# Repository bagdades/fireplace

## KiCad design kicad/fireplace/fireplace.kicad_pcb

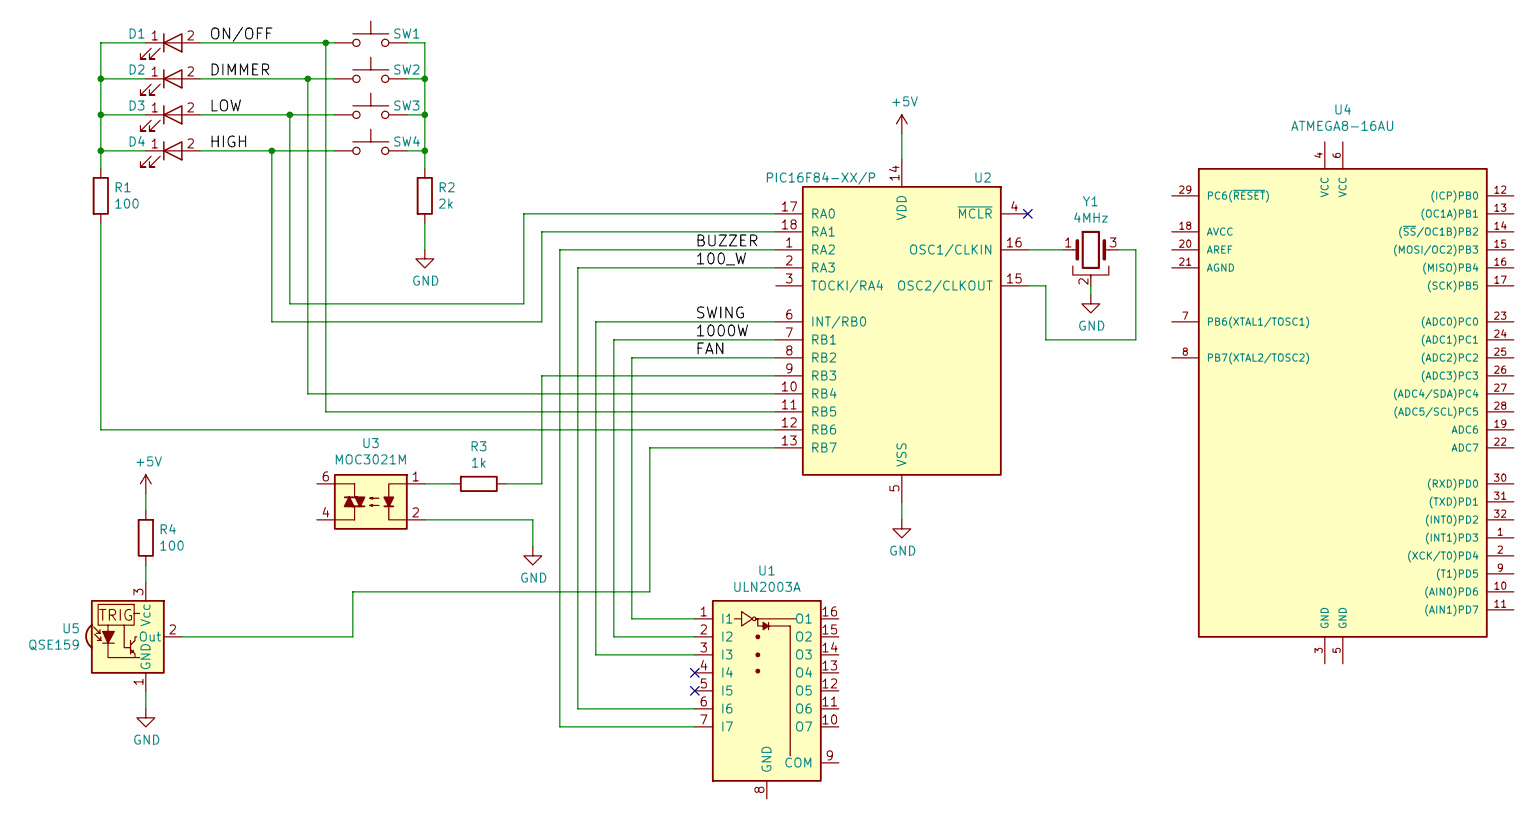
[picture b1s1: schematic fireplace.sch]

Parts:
D1, D2, D3, D4: LED; LED_D4.0mm
R1, R4: 100; R_Axial_DIN0309_L9.0mm_D3.2mm_P12.70mm_Horizontal
R2: 2k; R_Axial_DIN0309_L9.0mm_D3.2mm_P12.70mm_Horizontal
R3: 1k; R_Axial_DIN0309_L9.0mm_D3.2mm_P12.70mm_Horizontal
SW1, SW2, SW3, SW4: SW_Push; SW_PUSH_6mm_h5mm
U1: ULN2003A; DIP-16_W7.62mm
U2: PIC16F84-XX/P; DIP-18_W7.62mm
U3: MOC3021M; DIP-6_W7.62mm
U4: ATMEGA8-16AU; LQFP-32_7x7mm_Pitch0.8mm
U5: QSE159; ONSemi_QSE15x
Y1: 4MHz; Resonator-3pin_w8.0mm_h3.5mm

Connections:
+5V: R4.2, U2.14 (VDD)
/100_W: U1.6 (I6), U2.2 (RA3)
/1000W: U1.2 (I2), U2.7 (RB1)
/BUZZER: U1.7 (I7), U2.1 (RA2)
/DIMMER: D2.2 (A), SW2.1, U2.10 (RB4)
/FAN: U1.1 (I1), U2.8 (RB2)
/HIGH: D4.2 (A), SW4.1, U2.18 (RA1)
/LOW: D3.2 (A), SW3.1, U2.17 (RA0)
/ON/OFF: D1.2 (A), SW1.1, U2.11 (RB5)
/SWING: U1.3 (I3), U2.6 (INT/RB0)
GND: R2.2, U2.5 (VSS), U3.2, U5.1 (GND), Y1.2
unnamed: D1.1 (K), D2.1 (K), D3.1 (K), D4.1 (K), R1.1
unnamed: R1.2, U2.12 (RB6)
unnamed: R2.1, SW1.2, SW2.2, SW3.2, SW4.2
unnamed: R3.1, U2.9 (RB3)
unnamed: R3.2, U3.1
unnamed: R4.1, U5.3 (Vcc)
unnamed: U2.13 (RB7), U5.2 (Out)
unnamed: U2.15 (OSC2/CLKOUT), Y1.3
unnamed: U2.16 (OSC1/CLKIN), Y1.1

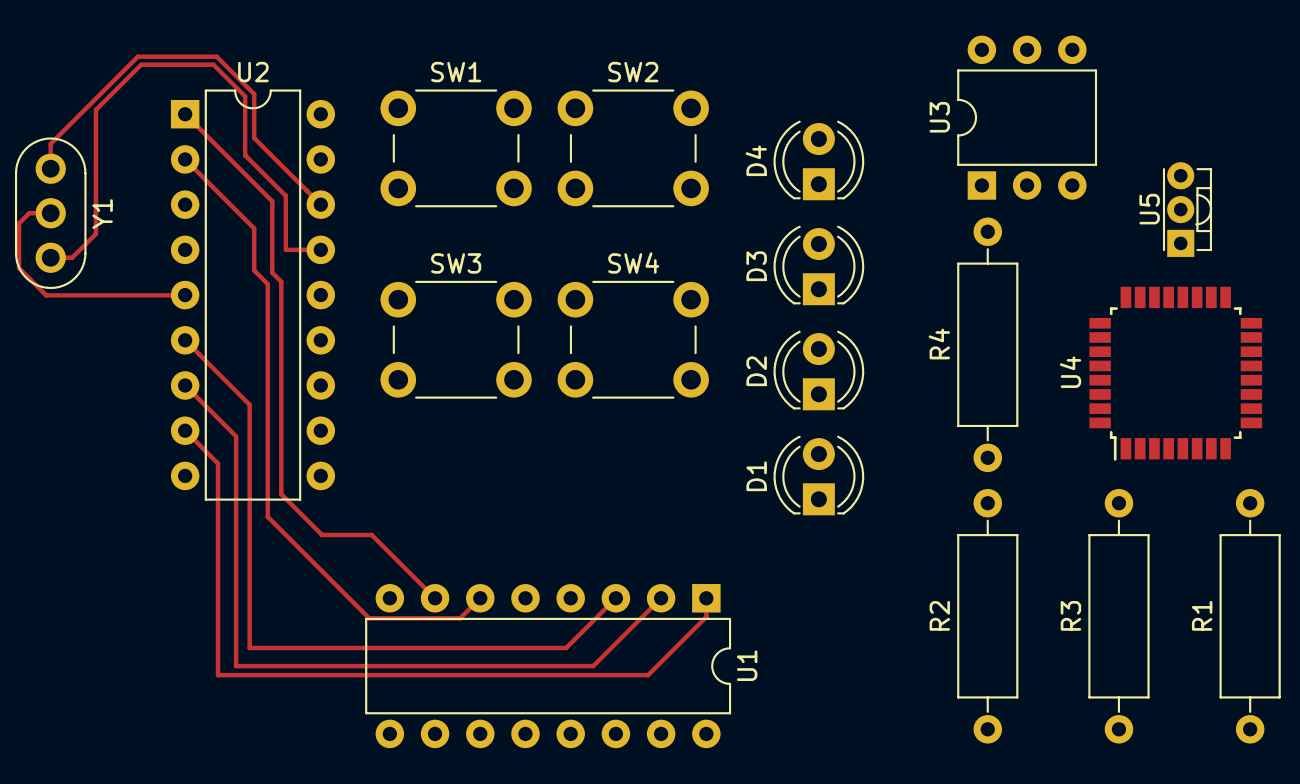
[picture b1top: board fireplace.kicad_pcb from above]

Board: 2 copper layers, 18 parts (0 on the bottom side), 20 nets.

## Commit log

2017-10-27 Start projects
2017-10-27 Add Kicad schematic
2017-10-28 Add key function
2017-10-28 Function led update
2017-10-29 Start IR discovery
2017-10-29 Test work on hard, and correct key and led functions
2017-10-31 Fix key
2017-10-31 Set int0 to ir pin
2017-11-01 Start IR code
2017-11-02 Error IR
2017-11-02 Corect Timer2 prescaller
2017-11-02 Good IR work
2017-11-02 Add buzzer, out controll
2017-11-03 Set OUT_LED output
